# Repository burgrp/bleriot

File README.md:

# BleRiot

BleRiot is a compact request/response protocol for reading and writing named
integer registers on low-power RF nodes. A Linux hub polls the nodes and bridges
their registers to an external [Registry](https://github.com/burgrp/reg)
service. Registry change requests become idempotent absolute register
assignments.

The radio uses GFSK with BLE Coded PHY framing: S8 provides about 125 kbps for
maximum range, while S2 provides about 500 kbps at shorter range. It is not a
standard BLE connection: BleRiot selects raw RF channels and uses its own fixed
packet, addressing, transaction, and encryption rules.

## Architecture

```text
Registry service
       ^  provide values / consume assignments
       |
Linux hub: lib/site
  - inventory and per-node XTEA keys
  - one polling scheduler per RF channel
  - retries, liveness, Registry publication, diagnostics
       |
       | USB HID
       v
MCP2210 --SPI-- PAN211x radio   one passive dongle per active channel
       |
       | BLE-compatible raw RF framing (S8 ~125 kbps / S2 ~500 kbps)
       v
nodes sharing that channel
```

Each independent group uses one half-duplex RX/TX radio channel. The hub permits
one in-flight `GET` or `SET` transaction on a channel, including its retries and
reply wait. Different channels have independent transaction lanes and run
concurrently.

The [MCP2210 dongle](dongle/mcp2210) is a passive USB-to-SPI bridge driving a
PAN211x. It has no microcontroller, firmware, keys, or protocol state. All
protocol and scheduling logic runs on the Linux host.

## Protocol Summary

Every packet is 13 bytes: a four-byte plaintext source address, a one-byte
plaintext packet version, and one XTEA-encrypted eight-byte block containing
type, flags, register tag, and raw `int32` value. The four packet types are:

| Value | Type | Transaction |
|---:|---|---|
| `0x00` | `GET` | Hub asks for a register; node replies with `VALUE`. |
| `0x01` | `VALUE` | Node returns the current value or `NULL`. |
| `0x02` | `SET` | Hub assigns an absolute value or `NULL`; node replies with `ACK`. |
| `0x03` | `ACK` | Node confirms receipt of a `SET`; resulting state may settle asynchronously. |

There is no transaction token. Channel ownership serializes requests, and the
hub accepts a reply only when its source, register, and response type match the
active transaction. See the [authoritative protocol specification](lib/README.md)
for packet fields, pacing, retry, and register semantics.

## Repository Layout

| Path | Responsibility |
|---|---|
| [lib](lib) | The Go library module and authoritative protocol specification. |
| [lib/shared](lib/shared) | Build-tag-free packages shared by host and TinyGo: packet codec, configuration, inventory, conversions, and chip profiles. |
| [lib/node](lib/node) | Allocation-free firmware runtime for `GET` and `SET`. |
| [lib/site](lib/site) | Linux host engine, polling bridge, diagnostics, CLI, and radio drivers. |
| [example/bob](example/bob) | Reference device type, TinyGo firmware, and inventory-driven host executable. |
| [dongle/mcp2210](dongle/mcp2210) | Passive MCP2210/PAN211x dongle hardware and Linux udev rule. |
| [dongle/py32f403](dongle/py32f403) | Smart-dongle hardware design. |
| [bob](bob) | Reference node PCB. |
| [sub/hw-kicad](sub/hw-kicad) | Shared KiCad symbols and footprints. |

Register identity is a permanent, nonzero per-device-type `uint16` tag.
Deployments are ordinary Go `inventory.Inventory` values; there is no JSON
descriptor. `bleriot node build` generates the TinyGo entry point that bakes one
instance's address, key, channel, spread factor, and config into its firmware.

## Quick Start

Run the reference hub against a Registry service:

```sh
cd example/bob
go run ./cmd/dev hub --registry http://localhost:8080 --sweep-interval 1s
```

The hub discovers MCP2210 dongles and assigns them to inventory channels. It
starts with no dongle attached and brings channels online as dongles appear.
Install the shipped udev rule first so the hub can use `/dev/hidraw*` without
root; see [USB access](lib/site/README.md#usb-access).

Useful optional flags include `--timeout 50ms`, `--retries 3`,
`--diagnostics bleriot`, and `--diag-interval 1s`. The persistent `--debug` flag
may appear before or after the subcommand:

```sh
go run ./cmd/dev --debug hub --registry http://localhost:8080 --diagnostics bleriot
```

Create and flash an inventory identity from the reference module:

```sh
cd example/bob
go run ./cmd/dev node new
go run ./cmd/dev node build --name bob --flash --rtt
```

`node new` works offline and prints an `inventory.Instance` stub with a random
nonzero address and XTEA key. `node build` selects the inventory instance,
generates its baked firmware entry point, and follows the build and pyOCD policy
declared by the device type's firmware manifest.

The reference firmware exposes `bob.led` as the single writable LED register;
it controls the green LED. The red LED is reserved for connection status: off
while hub packets are arriving, and a 200 ms pulse once per second after five
seconds without a packet.

## Documentation

- [Protocol specification](lib/README.md): authoritative wire format, RF,
  transactions, reliability, register model, and identity.
- [Host library](lib/site/README.md): inventory, commands, polling scheduler,
  Registry behavior, USB access, and diagnostics.
- [Diagnostic metrics](lib/site/DIAGNOSTICS.md): schema 9 catalog, accounting
  rules, and Prometheus examples.

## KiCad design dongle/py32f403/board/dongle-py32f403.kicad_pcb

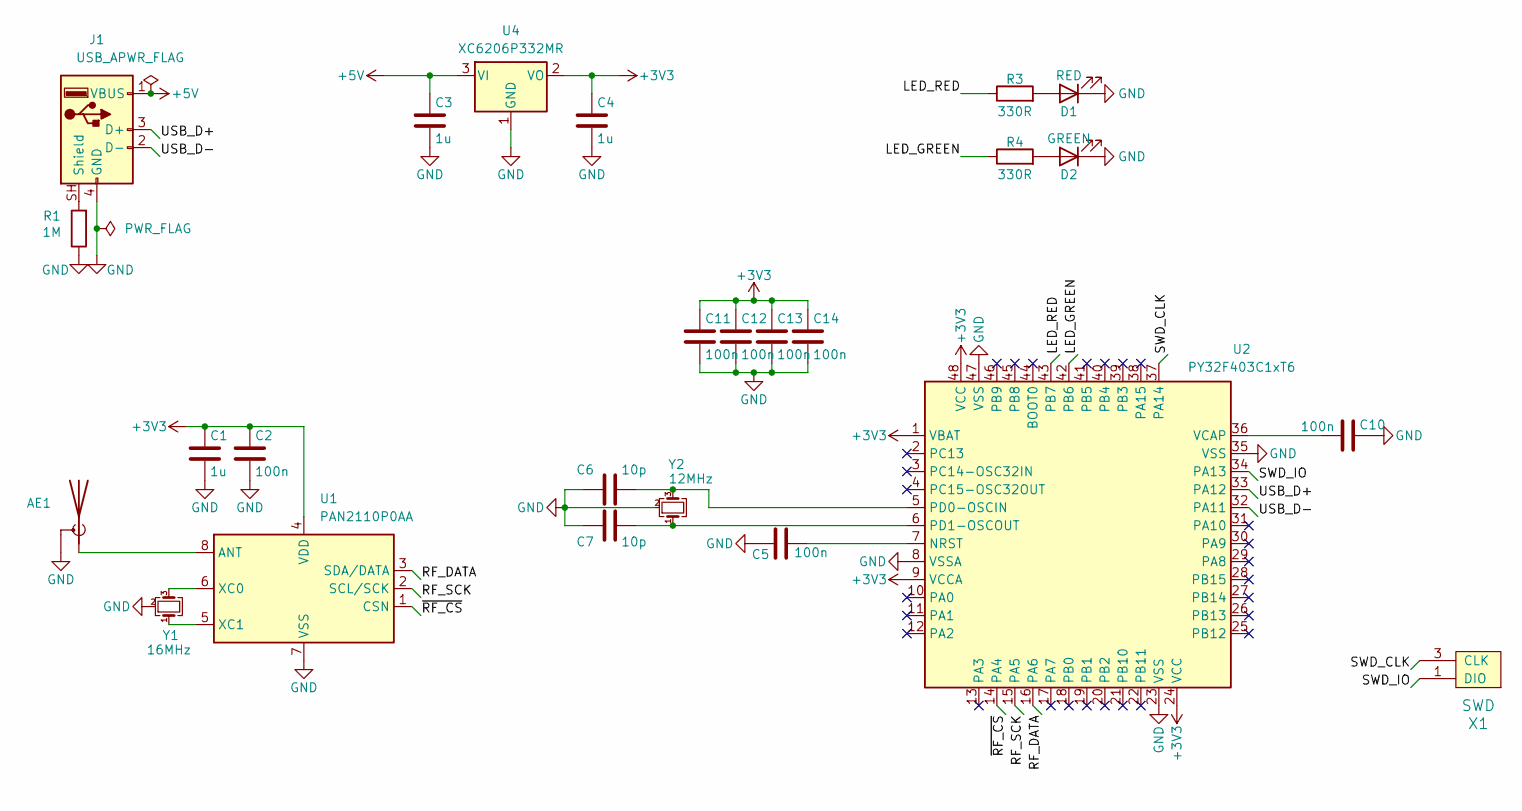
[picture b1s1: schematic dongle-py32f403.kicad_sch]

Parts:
AE1: Antenna_Shield; Texas_SWRA117D_2.4GHz_Right
C1, C3, C4: 1u; C_0805_2012Metric
C2, C5, C10, C11, C12, C13, C14: 100n; C_0805_2012Metric
C6, C7: 10p; C_0805_2012Metric
D1: RED; LED_0805_2012Metric
D2: GREEN; LED_0805_2012Metric
J1: USB_A; USB_A_CNCTech_1001-011-01101_Horizontal
R1: 1M; R_0805_2012Metric
R3, R4: 330R; R_0805_2012Metric
U1: PAN2110P0AA; SOIC-8_3.9x4.9mm_P1.27mm
U2: PY32F403C1xT6; LQFP-48_7x7mm_P0.5mm
U4: XC6206P332MR; SOT-23-3
X1: SWD
Y1: 16MHz; Crystal_SMD_3225-4Pin_3.2x2.5mm
Y2: 12MHz; Crystal_SMD_3225-4Pin_3.2x2.5mm

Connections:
+3V3: C1.1, C2.1, C4.1, C11.1, C12.1, C13.1, C14.1, U1.4 (VDD), U2.1 (VBAT), U2.9 (VCCA), U2.24 (VCC), U2.48 (VCC), U4.2 (VO)
+5V: C3.1, J1.1 (VBUS), U4.3 (VI)
/LED_GREEN: R4.1, U2.42 (PB6)
/LED_RED: R3.1, U2.43 (PB7)
/RF_DATA: U1.3 (SDA/DATA), U2.16 (PA6)
/RF_SCK: U1.2 (SCL/SCK), U2.15 (PA5)
/SWD_CLK: U2.37 (PA14), X1.3 (CLK)
/SWD_IO: U2.34 (PA13), X1.1 (DIO)
/USB_D+: J1.3 (D+), U2.33 (PA12)
/USB_D-: J1.2 (D-), U2.32 (PA11)
/~RF_CS: U1.1 (CSN), U2.14 (PA4)
GND: AE1.2 (Shield), C1.2, C2.2, C3.2, C4.2, C5.1, C6.2, C7.2, C10.1, C11.2, C12.2, C13.2, C14.2, D1.1 (K), D2.1 (K), J1.4 (GND), R1.1, U1.7 (VSS), U2.8 (VSSA), U2.23 (VSS), U2.35 (VSS), U2.47 (VSS), U4.1 (GND), X1.2 (GND), Y1.2 (G), Y1.4 (G), Y2.2 (G), Y2.4 (G)
unnamed: AE1.1 (A), U1.8 (ANT)
unnamed: D1.2 (A), R3.2
unnamed: D2.2 (A), R4.2
unnamed: J1.SH (Shield), R1.2
unnamed: U1.6 (XC0), Y1.3
unnamed: U1.5 (XC1), Y1.1
unnamed: C5.2, U2.7 (NRST)
unnamed: C6.1, U2.5 (PD0-OSCIN), Y2.3
unnamed: C7.1, U2.6 (PD1-OSCOUT), Y2.1
unnamed: C10.2, U2.36 (VCAP)

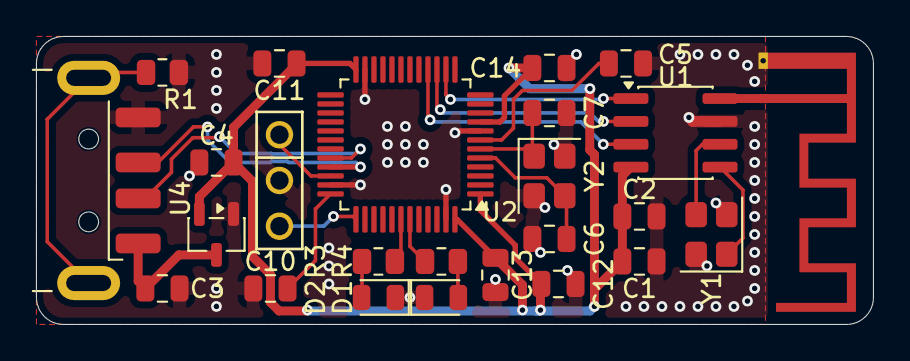
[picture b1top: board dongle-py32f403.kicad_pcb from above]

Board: 2 copper layers, 46.5 x 16.0 mm, 25 parts (0 on the bottom side), 22 nets.

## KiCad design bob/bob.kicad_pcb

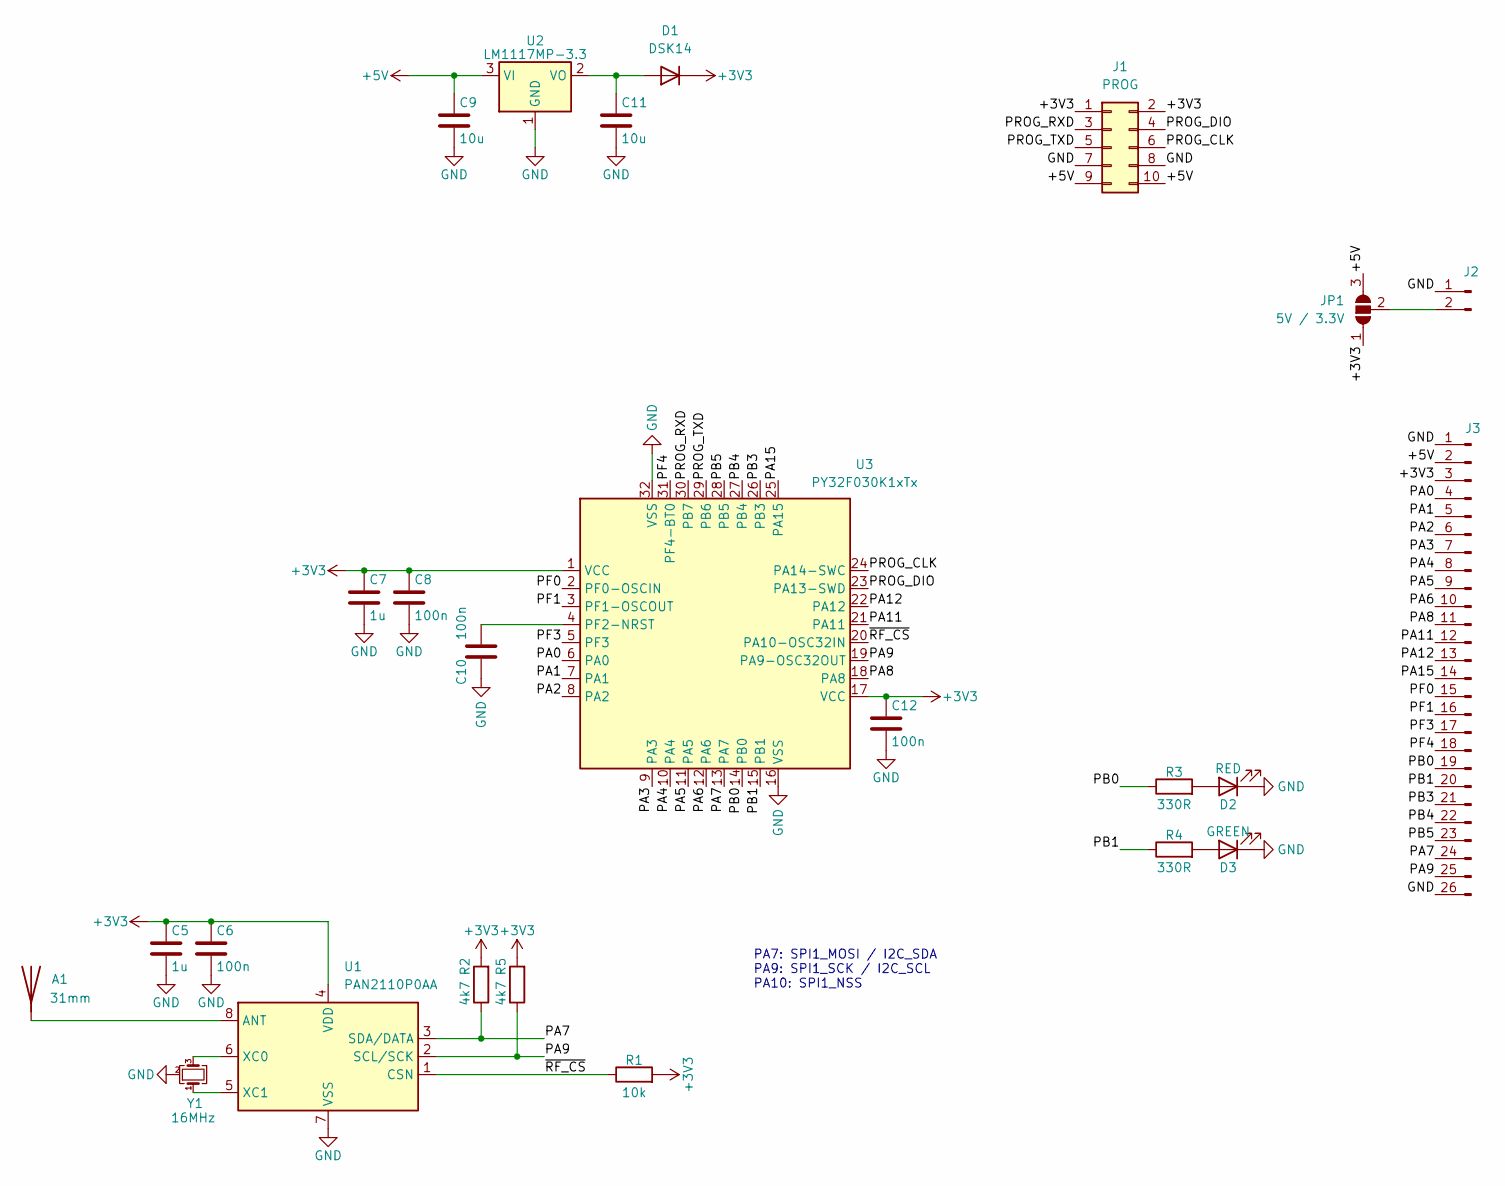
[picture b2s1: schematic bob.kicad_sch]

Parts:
A1: 31mm; Wire antena 2.4GHz
C5, C7: 1u; C_0805_2012Metric
C6, C8, C10, C12: 100n; C_0805_2012Metric
C9, C11: 10u; C_0805_2012Metric
D1: DSK14; D_SOD-123
D2: RED; LED_0805_2012Metric
D3: GREEN; LED_0805_2012Metric
J1: PROG; PinHeader_2x05_P2.54mm_Vertical
J2: PWR; PinHeader_1x02_P2.54mm_Vertical
J3: BB; PinHeader_1x26_P2.54mm_Vertical
JP1: 5V / 3.3V; SolderJumper-3_P2.0mm_Open_TrianglePad1.0x1.5mm
R1: 10k; R_0805_2012Metric
R2, R5: 4k7; R_0805_2012Metric
R3, R4: 330R; R_0805_2012Metric
U1: PAN2110P0AA; SOIC-8_3.9x4.9mm_P1.27mm
U2: LM1117MP-3.3; SOT-223-3_TabPin2
U3: PY32F030K1xTx; LQFP-32_7x7mm_P0.8mm
Y1: 16MHz; Crystal_SMD_3225-4Pin_3.2x2.5mm

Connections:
+3V3: C5.1, C6.1, C7.1, C8.1, C12.1, D1.1 (K), J1.1, J1.2, J3.3, JP1.1 (A), R1.2, R2.2, R5.2, U1.4 (VDD), U3.1 (VCC), U3.17 (VCC)
+5V: C9.1, J1.9, J1.10, J3.2, JP1.3 (B), U2.3 (VI)
/PA0: J3.4, U3.6 (PA0)
/PA1: J3.5, U3.7 (PA1)
/PA2: J3.6, U3.8 (PA2)
/PA3: J3.7, U3.9 (PA3)
/PA4: J3.8, U3.10 (PA4)
/PA5: J3.9, U3.11 (PA5)
/PA6: J3.10, U3.12 (PA6)
/PA7: J3.24, R2.1, U1.3 (SDA/DATA), U3.13 (PA7)
/PA8: J3.11, U3.18 (PA8)
/PA9: J3.25, R5.1, U1.2 (SCL/SCK), U3.19 (PA9-OSC32OUT)
/PA11: J3.12, U3.21 (PA11)
/PA12: J3.13, U3.22 (PA12)
/PA15: J3.14, U3.25 (PA15)
/PB0: J3.19, R3.1, U3.14 (PB0)
/PB1: J3.20, R4.1, U3.15 (PB1)
/PB3: J3.21, U3.26 (PB3)
/PB4: J3.22, U3.27 (PB4)
/PB5: J3.23, U3.28 (PB5)
/PF0: J3.15, U3.2 (PF0-OSCIN)
/PF1: J3.16, U3.3 (PF1-OSCOUT)
/PF3: J3.17, U3.5 (PF3)
/PF4: J3.18, U3.31 (PF4-BT0)
/PROG_CLK: J1.6, U3.24 (PA14-SWC)
/PROG_DIO: J1.4, U3.23 (PA13-SWD)
/PROG_RXD: J1.3, U3.30 (PB7)
/PROG_TXD: J1.5, U3.29 (PB6)
/~RF_CS: R1.1, U1.1 (CSN), U3.20 (PA10-OSC32IN)
GND: C5.2, C6.2, C7.2, C8.2, C9.2, C10.2, C11.2, C12.2, D2.1 (K), D3.1 (K), J1.7, J1.8, J2.1, J3.1, J3.26, U1.7 (VSS), U2.1 (GND), U3.16 (VSS), U3.32 (VSS), Y1.2 (G), Y1.4 (G)
unnamed: A1.1 (A), U1.8 (ANT)
unnamed: C11.1, D1.2 (A), U2.2 (VO)
unnamed: D2.2 (A), R3.2
unnamed: D3.2 (A), R4.2
unnamed: J2.2, JP1.2 (C)
unnamed: U1.6 (XC0), Y1.3
unnamed: U1.5 (XC1), Y1.1
unnamed: C10.1, U3.4 (PF2-NRST)

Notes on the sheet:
PA7: SPI1_MOSI / I2C_SDA PA9: SPI1_SCK / I2C_SCL PA10: SPI1_NSS

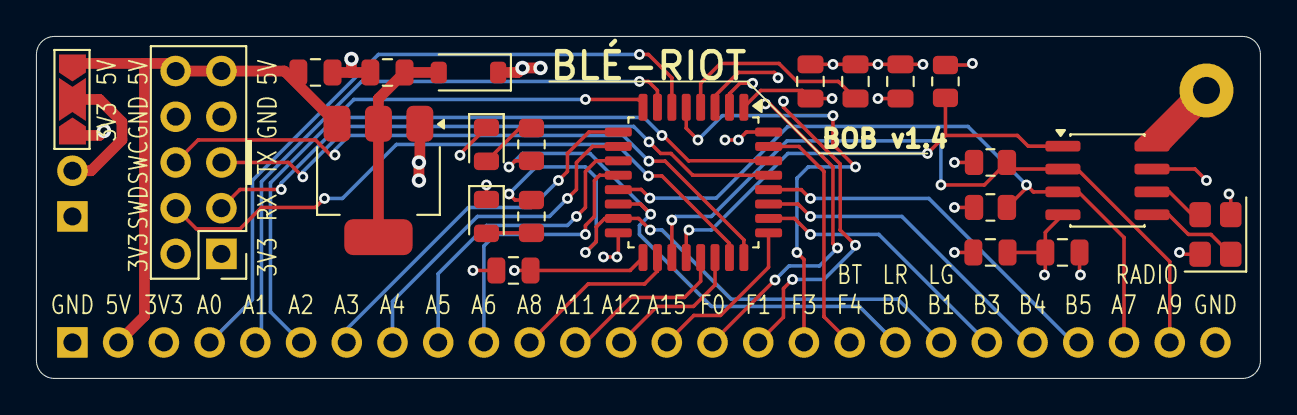
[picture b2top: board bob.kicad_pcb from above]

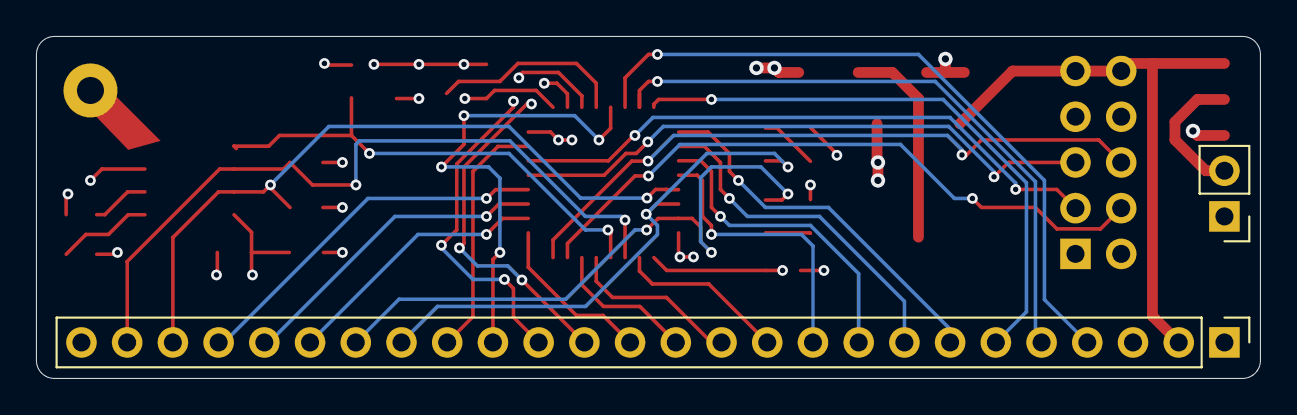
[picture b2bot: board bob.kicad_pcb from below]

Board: 4 copper layers, 68.0 x 19.0 mm, 25 parts (2 on the bottom side), 38 nets.

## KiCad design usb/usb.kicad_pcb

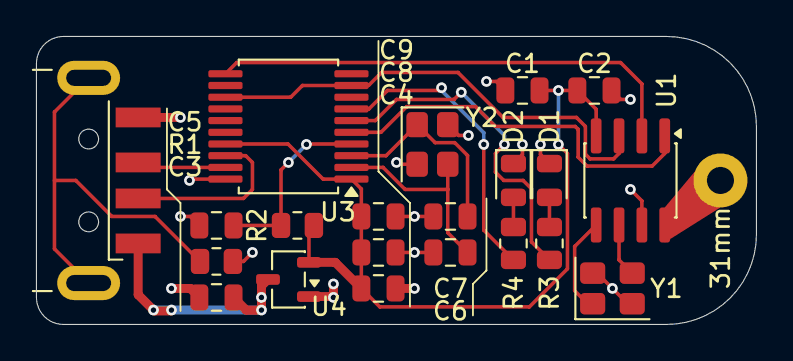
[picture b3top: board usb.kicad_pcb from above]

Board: 2 copper layers, 40.0 x 16.0 mm, 22 parts (0 on the bottom side), 19 nets.

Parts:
A1: 31mm; Wire antena 2.4GHz
C1, C3, C4, C8: 1u; C_0805_2012Metric
C2, C5, C9: 100n; C_0805_2012Metric
C6, C7: 10p; C_0805_2012Metric
D1: RED; LED_0805_2012Metric
D2: GREEN; LED_0805_2012Metric
J1: USB_A; USB_A_CNCTech_1001-011-01101_Horizontal
R1: 1M; R_0805_2012Metric
R2: 10k; R_0805_2012Metric
R3, R4: 330R; R_0805_2012Metric
U1: PAN2110P0AA; SOIC-8_3.9x4.9mm_P1.27mm
U3: MCP2210x-SS; SSOP-20_5.3x7.2mm_P0.65mm
U4: XC6206P332MR; SOT-23-3
Y1: 16MHz; Crystal_SMD_3225-4Pin_3.2x2.5mm
Y2: 12MHz; Crystal_SMD_3225-4Pin_3.2x2.5mm

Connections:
+3V3: C1.1, C2.1, C4.1, C8.1, C9.1, R2.1, U1.4 (VDD), U3.1 (VDD), U3.17 (VUSB), U4.2 (VO)
+5V: C3.1, J1.1 (VBUS), U4.3 (VI)
/LED_GREEN: R4.1, U3.7 (GP2)
/LED_RED: R3.1, U3.6 (GP1)
/RF_DATA: U1.3 (SDA/DATA), U3.9 (MOSI), U3.13 (MISO)
/RF_SCK: U1.2 (SCL/SCK), U3.11 (SCK)
/USB_D+: J1.3 (D+), U3.19 (D+)
/USB_D-: J1.2 (D-), U3.18 (D-)
/~RF_CS: U1.1 (CSN), U3.5 (GP0)
GND: C1.2, C2.2, C3.2, C4.2, C5.2, C6.2, C7.2, C8.2, C9.2, D1.1 (K), D2.1 (K), J1.4 (GND), R1.1, U1.7 (VSS), U3.20 (VSS), U4.1 (GND), Y1.2 (G), Y1.4 (G), Y2.2 (G), Y2.4 (G)
unnamed: A1.1 (A), U1.8 (ANT)
unnamed: D1.2 (A), R3.2
unnamed: D2.2 (A), R4.2
unnamed: J1.5 (Shield), R1.2
unnamed: U1.6 (XC0), Y1.3
unnamed: U1.5 (XC1), Y1.1
unnamed: C6.1, U3.2 (OSC1), Y2.3
unnamed: C7.1, U3.3 (OSC2), Y2.1
unnamed: C5.1, R2.2, U3.4 (~RST)

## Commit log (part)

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2026-01-06 update hw-kicad subproject to latest commit
2026-02-24 Add PAN211x I2C High-Level Analyzer implementation and documentation
2026-02-24 bob 1.3
2026-03-03 works
2026-03-30 LED resistors changed to 330R
2026-04-10 Add VSCode configuration files for Go development and enable Git integration
2026-04-19 reg def
2026-04-25 hub/node works
2026-04-27 Implement feature X to enhance user experience and fix bug Y in module Z
2026-04-27 Refactor code structure for improved readability and maintainability
2026-04-28 new driver works
2026-04-28 fix: add error handling for invalid RF channel in SetChannel function
2026-04-28 refactor: remove PAN211x High-Level Analyzer implementation and documentation
2026-05-01 both bb work
2026-05-01 BLE works
2026-05-03 update SpreadFactor to S8 for BLE long range configuration
2026-05-03 implement XTEA encryption for BleRiot packets and update main-ble to demonstrate codec usage
2026-05-03 refactor Device role handling to use Role type and improve logging
2026-05-03 refactor Device structure to remove Role type and enhance initialization methods
2026-05-29 update PROTOCOL.md and codec.go to reflect changes in packet structure and versioning
2026-05-29 refactor packet structure and update protocol documentation to reflect changes in PDU size and encryption method
2026-05-29 remove duplicate package declaration in main_test.go
2026-05-29 Refactor node descriptor handling to remove node name from shared descriptors and implement per-device instance files for node identities
2026-05-29 Refactor node descriptor to remove RF channel and node name from shared descriptors; update related instance file handling and tests
2026-05-29 feat: implement BleRiot identity handling and COBS framing protocol
    - Add identity management in hub/host/node with parsing functions for addresses and keys.
    - Introduce COBS framing protocol in hub/link for communication between host and modem.
    - Implement message framing and decoding logic in hub/link/frame for structured communication.
    - Create codec for BleRiot packets in protocol package, supporting encoding and decoding with XTEA encryption.
    - Add comprehensive tests for identity parsing, COBS framing, and protocol codec to ensure reliability.
2026-05-29 feat: add main modem implementation and initial Makefile for hub
2026-05-29 feat: add initial documentation for BleRiot modules including README files for hub/host, hub/fw, hub/link, and generator
2026-05-29 docs: enhance architecture diagram in README for clarity on data flow and protocols
2026-05-30 fix: update radio initialization log message for clarity
2026-05-30 feat: implement reconnecting Port for self-healing radio communication
    - Added Port struct to manage a reconnecting radio modem that handles transport loss and automatic reconnections.
    - Implemented methods for sending packets and managing received packets through a stable channel.
    - Introduced PortConfig for configuring the Port with necessary parameters like Open function, Channel, Addr, RecvBuffer, Backoff, and Logger.
    - Created tests for Port functionality, ensuring it starts disconnected, reconnects properly, and handles packet transmission.
    feat: add node descriptor and identity management
    - Introduced Descriptor struct to model a BleRiot node's register table, including methods for
2026-05-30 feat: implement "bleriot generate" command for generating node code and descriptors
    - Added generate.go to handle the "bleriot generate" subcommand, which generates firmware node code and hub descriptors from a JSON specification.
    - Introduced codegen package to encapsulate the logic for generating Go source code and JSON descriptors.
    - Implemented descriptor package to manage the authoring model for registers and allocate deterministic wire IDs.
    - Added tests for code generation and ID allocation to ensure correctness and determinism.
    - Updated main.go to include the new generate command in the CLI.
    - Removed outdated generator directory and example files as they are no longer needed.
2026-05-31 Refactor node descriptor handling and update generation process
    - Changed the generation of firmware node code to include a descriptor ID instead of a version hash.
    - Updated the JSON structure for node descriptors to remove versioning and use content-addressing based on descriptor IDs.
    - Modified the CLI commands to reflect changes in argument handling and output file naming conventions.
    - Enhanced error handling for loading descriptors and nodes, ensuring proper validation of descriptor IDs.
    - Updated tests to align with the new descriptor ID structure and ensure comprehensive coverage of changes.
    - Removed deprecated version fields from descriptor files and adjusted related documentation.
2026-05-31 sketch
2026-05-31 feat: add chip provisioning support and enhance device onboarding process
2026-05-31 Refactor bridge and engine for NULL register handling and improve protocol
    - Updated Transactor interface to include SetNull method for clearing registers.
    - Modified serveRegister in bridge to handle nil requests by invoking SetNull.
    - Changed Set method in Transactor to return an error instead of an Update.
    - Enhanced Engine to support SetNull and adjusted transaction handling for ACK responses.
    - Updated protocol to define ACK type for SET acknowledgments.
    - Added tests for SetNull functionality and ensured proper handling of NULL values in device logic.
2026-05-31 fix: update key for lab configuration and increase stack size in Makefile
2026-05-31 feat: implement liveness check for node subscriptions and report NULL on timeouts
2026-06-17 cleanup
2026-06-18 feat(mcp2210): add pure-Go driver for MCP2210 USB-HID-to-SPI bridge
    - Implemented Device struct for managing MCP2210 connections.
    - Added functions for opening, closing, and communicating with the device.
    - Created SPIConfig struct for configuring SPI parameters.
    - Implemented methods for configuring GPIO, transferring data, and handling responses.
    feat(radio): implement BleRiot host radio over MCP2210
    - Created Radio struct to manage PAN211x communication via MCP2210.
2026-06-18 feat(bench): add benchmarking for end-to-end transaction latency between MCP2210 dongles
2026-06-18 Refactor dongle handling and introduce mcpdongle package
    - Updated Makefile to reflect new dongle scheme format.
    - Removed unnecessary package imports and cleaned up code in bench_test.go and dongles_test.go.
    - Enhanced dongle test setup to enforce scheme:selector format for environment variables.
    - Introduced mcpdongle package to encapsulate MCP2210 and PAN211x interactions.
    - Implemented new dongle interface to abstract radio operations.
    - Refactored radio package to utilize the new mcpdongle implementation.
2026-06-18 feat(bench): add benchmark test results for MCP2210 dongle functionality
2026-06-19 fix: add missing dependency for tinygo-drivers/pan211x in go.work
2026-06-19 Implement BLE provisioning page with fixed-size config and CRC validation
    - Introduced a new package `page` for handling the BLE provisioning page layout.
    - Defined the `Header` struct to encapsulate device identity and configuration details.
    - Implemented `Marshal` and `Unmarshal` functions for encoding and decoding the provisioning page.
    - Added CRC-32 validation to ensure data integrity during transmission.
    - Created unit tests for the `page` package to verify functionality and error handling.
    - Updated the `inventory` package to include a new `Channel` struct that combines channel number and spreading factor.
2026-06-19 refactoring
2026-06-19 feat: implement GUARD field for reply turnaround in protocol and engine
2026-06-19 refactor: streamline test setup and improve documentation for dongle tests
2026-06-19 feat: add benchmark results for functest with dongle configuration
2026-06-20 feat: update thermostat temperature range for Far and Near channels
2026-06-20 refactor: restructure thermostat module to use shared spec package and improve firmware organization
2026-06-20 feat: implement reconnecting dongle supervisor for improved device management
2026-06-20 Implement diagnostics and metrics for nodes and dongles
    - Add diagnostics functionality in the bridge package, including tests for rate calculations and trimming samples.
    - Enhance the hub command to support publishing diagnostic registers with a configurable namespace and averaging window.
    - Introduce metrics tracking in the engine for nodes, including cumulative counters for transmitted and received packets, timeouts, and online status.
    - Update the inventory structure to require unique channel names for diagnostics and validate channel configurations.
    - Extend the reconnecting dongle implementation to include diagnostic counters for connection state and traffic statistics.
    - Modify tests
2026-06-20 feat: add diagnostics support for hub RF health monitoring
2026-06-20 fix: update diagnostics register naming from 'nodes' to 'node' for consistency
2026-06-20 feat: update diagnostics to track uptime and downtime for dongles
2026-06-20 feat: refactor provisioning page handling and enhance chip profile consistency
2026-06-20 feat: update thermostat package usage and restore VSCode settings
2026-06-20 Refactor host package: remove chip management and provisioning logic
    - Deleted chip.go and chip_test.go as they are no longer needed.
    - Removed host.go, hub.go, new.go, probe.go, and provision.go files, consolidating functionality.
    - Updated start_test.go to include a new test case for duplicate dongles on the same channel.
    - Removed all references to the chip management and provisioning logic, streamlining the host package.
2026-06-20 feat: implement BleRiot thermostat firmware for BOB breakout board
2026-06-22 refactor: update documentation references from PROTOCOL.md to protocol/README.md
2026-06-22 feat: add initial implementation of thermostat device in device.go
2026-06-23 feat: implement exponential backoff for unanswered seeding GETs in Bridge
2026-06-23 Code size optimization
2026-06-23 chore: remove commented-out example device configurations from main.go
2026-06-23 shared package
2026-06-23 Implement firmware-side BleRiot runtime with radio communication and device management
    - Added `node` package containing the core runtime for managing radio communication and device interactions.
    - Implemented `Node` struct to handle device state, radio communication, and protocol management.
    - Created interfaces for `Radio` and `Device` to abstract communication and device operations.
    - Developed methods for handling GET, SET, and WATCH requests, including subscription management and notification of state changes.
    - Introduced a testing suite with a `fakeRadio` and `fakeDevice` to simulate and validate the runtime behavior.
    - Ensured memory efficiency by avoiding allocations during steady-s
2026-06-23 chore: remove unused dependencies from go.mod and go.sum
2026-06-23 refactor: restructure repository to unify under a single Go library module
    - Transitioned from a multi-module mono-repo to a single module `lib` that encapsulates the shared wire format, node firmware runtime, and host hub.
    - Updated README.md to reflect the new structure, including paths and descriptions for each component.
    - Adjusted documentation references throughout the codebase to point to the new module structure.
    - Enhanced clarity in comments and documentation regarding the protocol specification and its components.
    - Ensured all instances of protocol references in the code are updated to reflect the new documentation paths.
2026-06-25 feat: update hub to automatically discover and assign USB radio dongles; remove --dongle flag refactor: change chip references to PY32F030x8 across documentation and code
2026-06-25 fix: update SetChannel calls to SetChannelRF for improved functionality
2026-06-26 feat: add PAN211x node support with StartNode function
2026-06-26 feat: add new commands for hub management and update dependencies
